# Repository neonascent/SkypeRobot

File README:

Designs and code for the SkypeRobot by Josh Harle.
For more information see http://tacticalspace.org/archives/skyperobot/ 

This projectis licensed under a Creative Commons Attribution License.

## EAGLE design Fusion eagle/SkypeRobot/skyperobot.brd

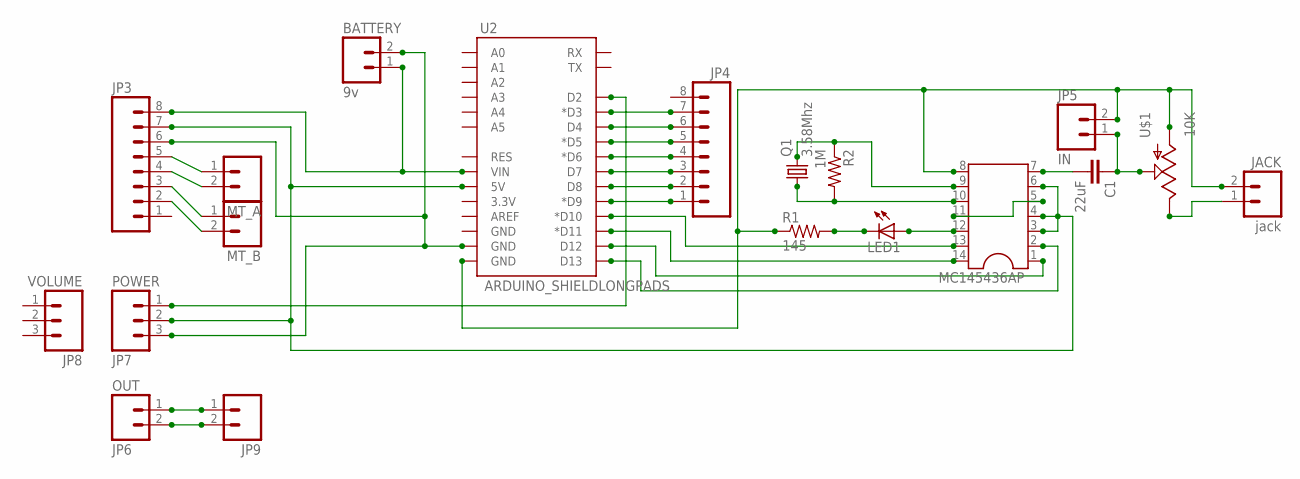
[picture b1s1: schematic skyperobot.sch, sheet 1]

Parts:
BATTERY: 9v; MOLEX-1X2
C1: 22uF; CAP-PTH-SMALL
JACK: jack; 1X02_LOCK_LONGPADS
JP3, JP4: M08LONGPADS; 1X08_LONGPADS
JP5: IN; 1X02
JP6: OUT; 1X02
JP7: POWER; 1X03
JP8: VOLUME; 1X03
JP9: M02POLAR; MOLEX-1X2
LED1: LED3MM
MC145436AP: DIL14
MT_A: M02POLAR; MOLEX-1X2
MT_B: M02POLAR; MOLEX-1X2
Q1: 3.58Mhz; HC18U-H
R1: 145; AXIAL-0.3
R2: 1M; AXIAL-0.3
U2: ARDUINO_SHIELDLONGPADS; DUEMILANOVE_SHIELD_LONGPADS_NOHOLES
U$1: 10K; TRIM_POT_10MM

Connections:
MT_A: JACK.2, JP5.2, MC145436AP.8, R1.P$1 (1), U2.GND@0 (GND), U$1.3 (A)
unnamed: MC145436AP.10, Q1.1, R2.P$2 (2)
unnamed: MC145436AP.5, MC145436AP.11
unnamed: JP3.7, JP7.2, MC145436AP.3, MC145436AP.4, MC145436AP.6, U2.5V
unnamed: JP3.5, MT_A.1
unnamed: JP3.4, MT_A.2
unnamed: JP3.3, MT_B.1
unnamed: JP3.2, MT_B.2
unnamed: C1.2, MC145436AP.7
unnamed: C1.1, JP5.1, U$1.1 (S)
unnamed: JP7.1, U2.D2
unnamed: BATTERY.1, JP3.8, U2.VIN
unnamed: BATTERY.2, JP3.6, JP7.3, U2.GND@1 (GND)
unnamed: LED1.K (C), R1.P$2 (2)
unnamed: JP4.7, U2.D3 (*D3)
unnamed: JP4.6, U2.D4
unnamed: JP4.5, U2.D5 (*D5)
unnamed: JP4.4, U2.D6 (*D6)
unnamed: JP4.3, U2.D7
unnamed: JP4.2, U2.D8
unnamed: JP4.1, U2.D9 (*D9)
unnamed: LED1.A, MC145436AP.12
unnamed: MC145436AP.1, U2.D12
unnamed: JP6.1, JP9.1
unnamed: JP6.2, JP9.2
unnamed: MC145436AP.9, Q1.2, R2.P$1 (1)
unnamed: MC145436AP.2, U2.D13
unnamed: MC145436AP.14, U2.D11 (*D11)
unnamed: MC145436AP.13, U2.D10 (*D10)
unnamed: JACK.1, U$1.2 (E)

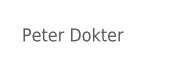
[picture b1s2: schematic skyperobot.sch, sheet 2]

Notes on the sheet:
Peter Dokter

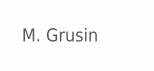
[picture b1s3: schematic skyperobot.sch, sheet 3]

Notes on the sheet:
M. Grusin

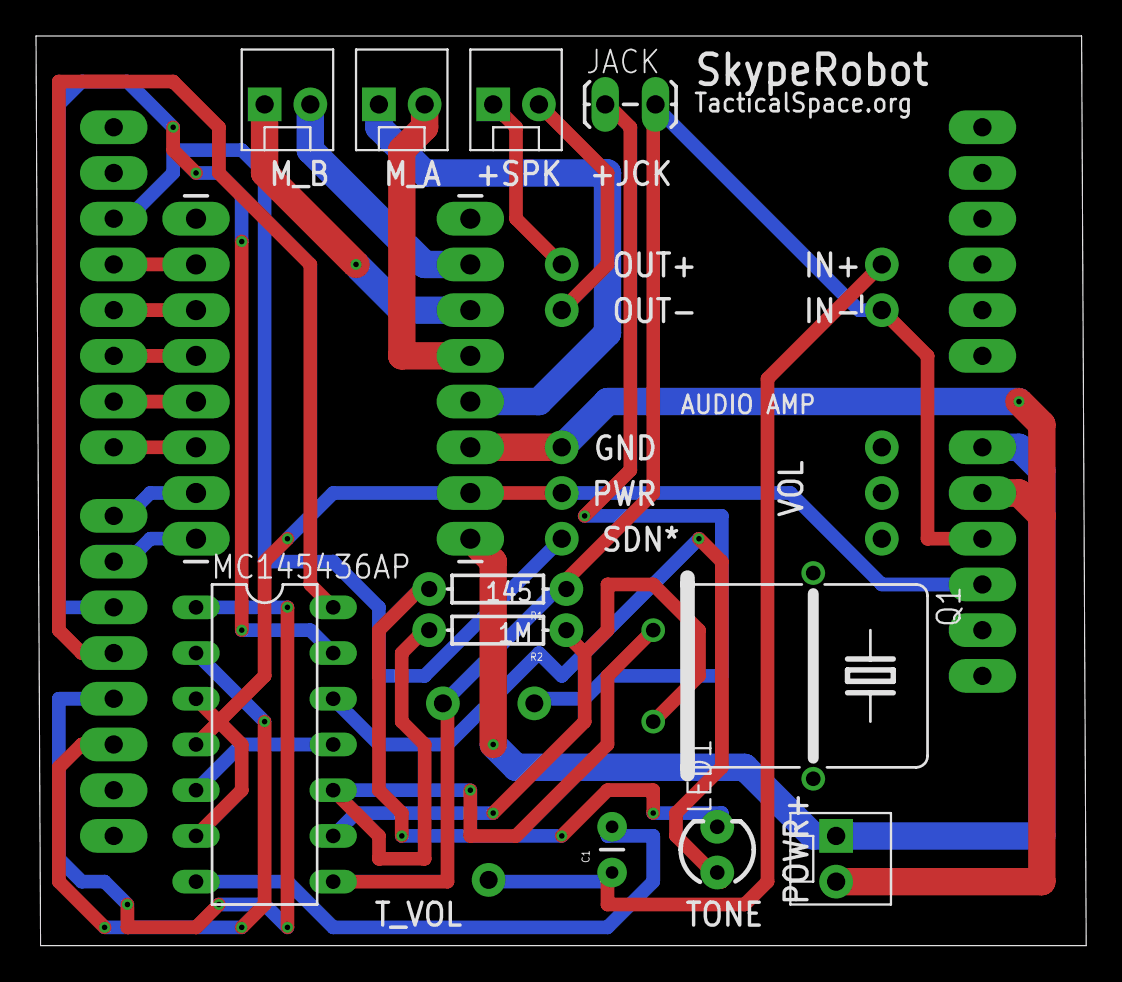
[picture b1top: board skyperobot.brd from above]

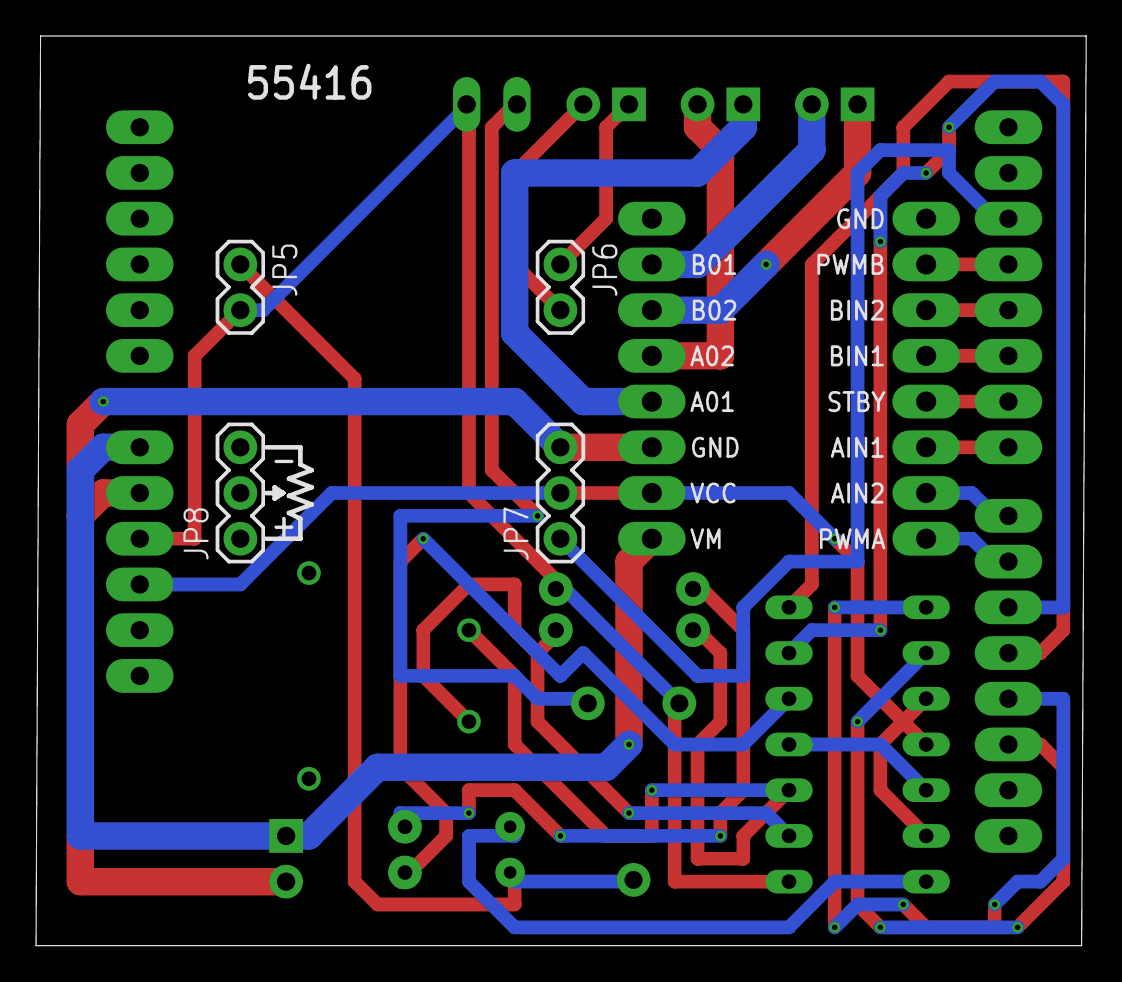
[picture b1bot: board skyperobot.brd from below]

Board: 2 copper layers, 58.3 x 50.5 mm, 19 parts (4 on the bottom side), 30 nets.

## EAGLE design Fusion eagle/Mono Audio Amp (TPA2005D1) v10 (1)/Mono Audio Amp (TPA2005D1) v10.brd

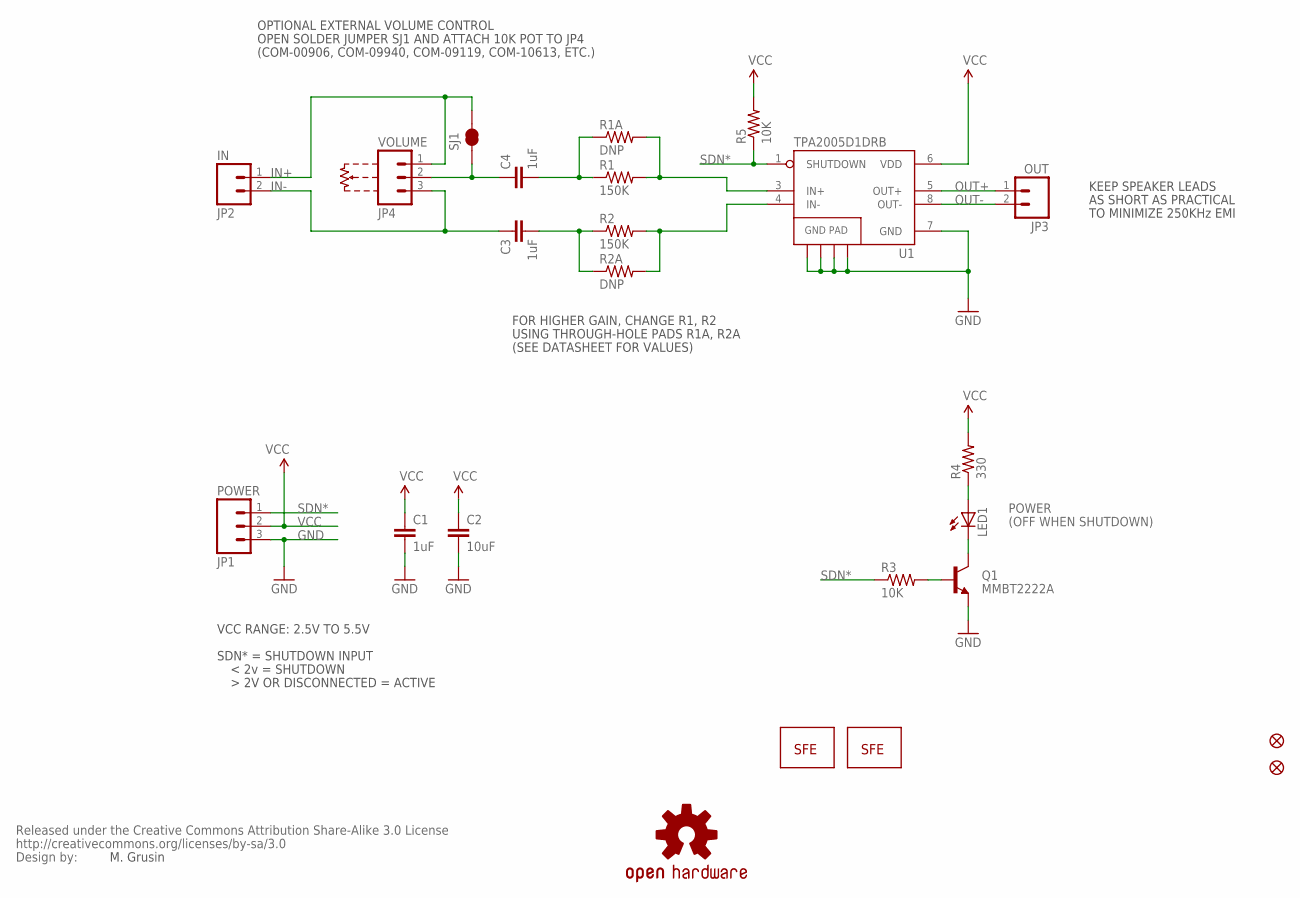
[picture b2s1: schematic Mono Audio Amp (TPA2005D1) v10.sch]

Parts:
C1, C3, C4: 1uF; 1206
C2: 10uF; 1206
JP1: POWER; 1X03
JP2: IN; 1X02
JP3: OUT; 1X02
JP4: VOLUME; 1X03
JP5, JP6: FIDUCIALUFIDUCIAL; MICRO-FIDUCIAL
LED1: LED0603; LED-0603
LOGO1: LOGO-SFENW2; SFE-NEW-WEB
LOGO2: LOGO-SFESK; SFE-LOGO-FLAME
Q1: MMBT2222A; SOT23-3
R1, R2: 150K; 0603-RES
R1A, R2A: DNP; AXIAL-0.3
R3, R5: 10K; 0603-RES
R4: 330; 0603-RES
SJ1: SOLDERJUMPERNC2; SJ_2S-NOTRACE
U1: TPA2005D1DRB; QFN-8_PAD
U$1: CREATIVE_COMMONS
U$2: OSHW-LOGOS; OSHW-LOGO-S

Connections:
GND: C1.2, C2.2, JP1.3, Q1.2 (E), U1.7 (GND), U1.10 (GND), U1.11 (GND), U1.12 (GND), U1.13 (GND)
IN+: JP2.1, JP4.1, SJ1.2
IN+AMP: R1.2, R1A.P$2 (2), U1.3 (IN+)
IN-: C3.1, JP2.2, JP4.3
IN-AMP: R2.2, R2A.P$2 (2), U1.4 (IN-)
unnamed: C4.1, JP4.2, SJ1.1
unnamed: C4.2, R1.1, R1A.P$1 (1)
unnamed: C3.2, R2.1, R2A.P$1 (1)
unnamed: LED1.C, Q1.3 (C)
unnamed: LED1.A, R4.1
unnamed: Q1.1 (B), R3.2
OUT+: JP3.1, U1.5 (OUT+)
OUT-: JP3.2, U1.8 (OUT-)
SDN*: JP1.1, R3.1, R5.1, U1.1 (SHUTDOWN)
VCC: C1.1, C2.1, JP1.2, R4.2, R5.2, U1.6 (VDD)

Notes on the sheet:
POWER
(OFF WHEN SHUTDOWN)
OPEN SOLDER JUMPER SJ1 AND ATTACH 10K POT TO JP4
OPTIONAL EXTERNAL VOLUME CONTROL
M. Grusin
FOR HIGHER GAIN, CHANGE R1, R2
USING THROUGH-HOLE PADS R1A, R2A
(SEE DATASHEET FOR VALUES)
SDN* = SHUTDOWN INPUT
< 2v = SHUTDOWN
VCC RANGE: 2.5V TO 5.5V
(COM-00906, COM-09940, COM-09119, COM-10613, ETC.)
KEEP SPEAKER LEADS
AS SHORT AS PRACTICAL
TO MINIMIZE 250KHz EMI

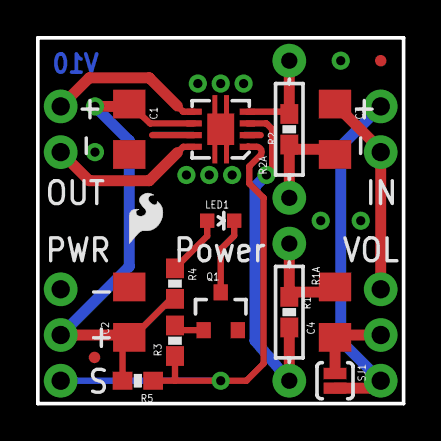
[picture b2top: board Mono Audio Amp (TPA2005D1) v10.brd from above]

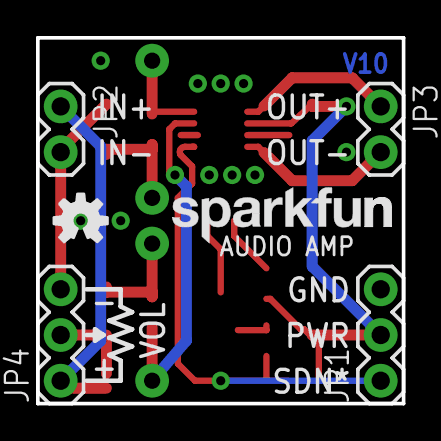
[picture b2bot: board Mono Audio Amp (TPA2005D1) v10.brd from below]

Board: 2 copper layers, 20.3 x 20.3 mm, 25 parts (6 on the bottom side), 15 nets.

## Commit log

2012-08-05 unicode weird character
2014-03-19 Eagle design
2014-03-19 Deleted link file
2014-03-21 Minor minor change to power plug position
    Should add switch too.
2017-05-08 update FYI

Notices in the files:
parts and their libraries:
SparkFun: Released under the Creative Commons Attribution Share-Alike 3.0 License
SparkFun: http://creativecommons.org/licenses/by-sa/3.0
SparkFun: Licensing: CC v3.0 Share-Alike You are welcome to use this library for commercial purposes.
